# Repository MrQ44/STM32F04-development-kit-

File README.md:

# STM32F04-development-kit-
This is a development kit using Stm32f04 microcontroller that I designed with Kicad
This is a simple kit using Stm32f04 microcontroller with GPIO pins provided for the user to use along with power indicator LED and a controllable LED

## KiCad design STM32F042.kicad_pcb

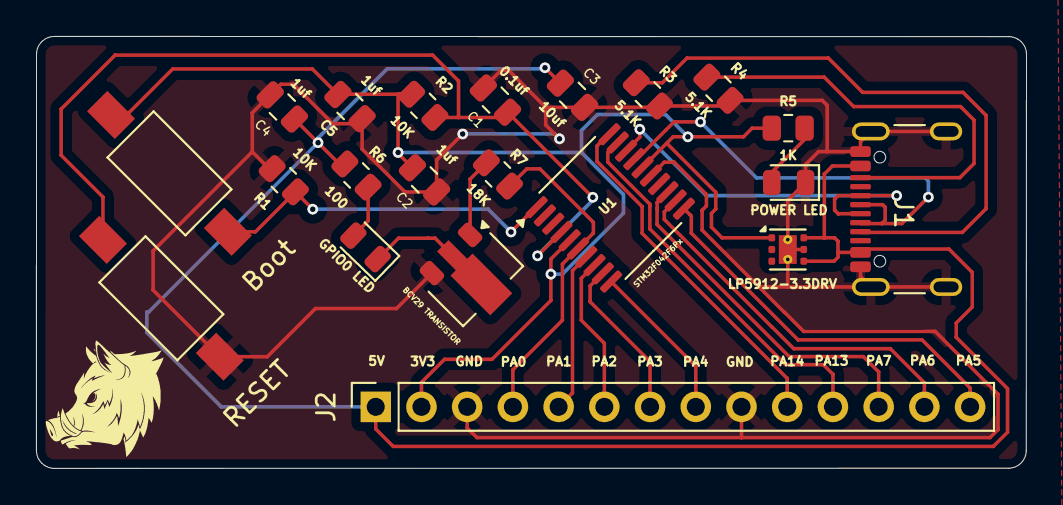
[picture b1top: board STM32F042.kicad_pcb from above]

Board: 2 copper layers, 55.0 x 24.0 mm, 21 parts (0 on the bottom side), 23 nets.

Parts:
BCV29 TRANSISTOR: BCV29; SOT-89-3
C1: 0.1uf; C_0805_2012Metric
C2, C4, C5: 1uf; C_0805_2012Metric
C3: 10uf; C_0805_2012Metric
GPIO0 LED: LED; LED_0805_2012Metric
J1: USB_C_Receptacle_USB2.0_16P; USB_C_Receptacle_GCT_USB4105-xx-A_16P_TopMnt_Horizontal
J2: Conn_01x14_Pin; PinSocket_1x14_P2.54mm_Vertical
POWER LED : LED; LED_0805_2012Metric
R1, R2: 10K; R_0805_2012Metric
R3, R4: 5.1K; R_0805_2012Metric
R5: 1K; R_0805_2012Metric
R6: 100; R_0805_2012Metric
R7: 18K; R_0805_2012Metric
SW1: Boot; SW_SPST_FSMSM
SW2: RESET; SW_SPST_FSMSM
U1: STM32F042F6Px; TSSOP-20_4.4x6.5mm_P0.65mm
U2: LP5912-3.3DRV; WSON-6-1EP_2x2mm_P0.65mm_EP1x1.6mm_ThermalVias

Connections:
/3V3: C2.1, C5.2, J2.2, R2.1, R5.1, SW1.2, U1.5 (VDDA), U1.16 (VDD), U2.1 (OUT)
/5v: C3.1, C4.2, J1.A4 (VBUS), J1.A9 (VBUS), J1.B4 (VBUS), J1.B9 (VBUS), J2.1, R6.1, U2.4 (EN), U2.6 (IN)
/PA0: J2.4, R7.1, U1.6 (PA0)
/PA1: J2.5, U1.7 (PA1)
/PA2: J2.6, U1.8 (PA2)
/PA3: J2.7, U1.9 (PA3)
/PA4: J2.8, U1.10 (PA4)
/PA5: J2.14, U1.11 (PA5)
/PA6: J2.13, U1.12 (PA6)
/PA7: J2.12, U1.13 (PA7)
/PA13: J2.11, U1.19 (PA13)
/PA14: J2.10, U1.20 (PA14)
/USB DM: J1.A7 (D-), J1.B7 (D-), U1.17 (PA9/PA11)
/USB DP: J1.A6 (D+), J1.B6 (D+), U1.18 (PA10/PA12)
GND: BCV29 TRANSISTOR.3 (E), C1.2, C2.2, C3.2, C4.1, C5.1, J1.A1 (GND), J1.A12 (GND), J1.B1 (GND), J1.B12 (GND), J1.S1 (SHIELD), J2.3, J2.9, POWER LED.1 (K), R1.2, R3.1, R4.1, SW2.1, U1.15 (VSSA), U2.5 (GND), U2.7 (EP)
unnamed: POWER LED.2 (A), R5.2
unnamed: GPIO0 LED.2 (A), R6.2
unnamed: BCV29 TRANSISTOR.2 (C), GPIO0 LED.1 (K)
unnamed: J1.A5 (CC1), R3.2
unnamed: J1.B5 (CC2), R4.2
unnamed: BCV29 TRANSISTOR.1 (B), R7.2
unnamed: C1.1, R2.2, SW2.2, U1.4 (NRST)
unnamed: R1.1, SW1.1, U1.1 (PB8)

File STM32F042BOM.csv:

Reference,Qty,Value,DNP,Exclude from BOM,Exclude from Board,Footprint,Datasheet
C1,1,0.1uf,,,,Capacitor_SMD:C_0805_2012Metric,~
"C2,C4,C5",3,1uf,,,,Capacitor_SMD:C_0805_2012Metric,~
C3,1,10uf,,,,Capacitor_SMD:C_0805_2012Metric,~
"D1,D2",2,LED,,,,LED_SMD:LED_0805_2012Metric,~
J1,1,USB_C_Receptacle_USB2.0_16P,,,,Connector_USB:USB_C_Receptacle_GCT_USB4105-xx-A_16P_TopMnt_Horizontal,https://www.usb.org/sites/default/files/documents/usb_type-c.zip
J2,1,Conn_01x14_Pin,,,,Connector_PinSocket_2.54mm:PinSocket_1x14_P2.54mm_Vertical,~
Q1,1,BCV29,,,,Package_TO_SOT_SMD:SOT-89-3,https://assets.nexperia.com/documents/data-sheet/BCV29_49.pdf
"R1,R2",2,10K,,,,Resistor_SMD:R_0805_2012Metric,~
"R3,R4",2,5.1K,,,,Resistor_SMD:R_0805_2012Metric,~
R5,1,1K,,,,Resistor_SMD:R_0805_2012Metric,~
R6,1,100,,,,Resistor_SMD:R_0805_2012Metric,~
R7,1,18K,,,,Resistor_SMD:R_0805_2012Metric,~
SW1,1,Boot,,,,Button_Switch_SMD:SW_SPST_FSMSM,~
SW2,1,RESET,,,,Button_Switch_SMD:SW_SPST_FSMSM,~
U1,1,STM32F042F6Px,,,,Package_SO:TSSOP-20_4.4x6.5mm_P0.65mm,https://www.st.com/resource/en/datasheet/stm32f042f6.pdf
U2,1,LP5912-3.3DRV,,,,Package_SON:WSON-6-1EP_2x2mm_P0.65mm_EP1x1.6mm_ThermalVias,http://www.ti.com/lit/ds/symlink/lp5912.pdf

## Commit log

2025-09-25 README.md
